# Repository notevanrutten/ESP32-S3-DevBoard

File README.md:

# ESP32-S3-DevBoard

A custom-built development board using the ESP32-S3 chip

## PlatformIO Setup

**NOTE:** This process only needs to be performed once for each development board

1. Download the Zadig driver installation program here: https://zadig.akeo.ie
2. Open Zadig, then click `Options -> List All Devices`
3. Select `USB JTAG/serial debug unit (Interface 0)` and change the driver to **USB Serial (CDC)**
4. Click "Upgrade/Downgrade Driver" (please note, this process may take a few minutes)
5. Select `USB JTAG/serial debug unit (Interface 2)` and change the driver to **libusbK**
6. Click "Upgrade/Downgrade Driver" (please note, this process may take a few minutes)
7. In PlatformIO, configure the platformio.ini file as follows:

   ```ini
    [env:esp32-s3-devboard]

    platform = https://github.com/platformio/platform-espressif32.git
    board = esp32-s3-devkitc-1
    framework = arduino

    upload_speed = 2000000
    monitor_speed = 115200

    debug_tool = esp-builtin
    debug_init_break = break setup
    build_type = debug

    ; enables CDC mode (activates USB-to-Serial)
    build_flags = -DARDUINO_USB_CDC_ON_BOOT=1
   ```

## USB Interface Options

### UART Uploading / Monitoring (Standard)

1. Click the PlatformIO icon on the Activity Bar (left)
2. Navigate to `PROJECT TASKS > esp32-s3-devboard > General > Upload and Monitor` (top left)
3. The firmware will be uploaded automatically and the serial output will be displayed in the terminal

### JTAG Debugging + VCOM Monitoring (Advanced)

1. Click the PlatformIO icon on the Activity Bar (left)
2. Navigate to `QUICK ACCESS > Debug > Start Debugging` (bottom left), or press `F5`
3. The firmware will be uploaded automatically and the debug toolbar will appear (top middle)
4. Use the debug toolbar to Pause/Unpause, Restart, or Stop the program (also has code stepping)
5. To view the serial output while code is unpaused, click `PlatformIO: Serial Monitor` on the Status Bar (bottom)

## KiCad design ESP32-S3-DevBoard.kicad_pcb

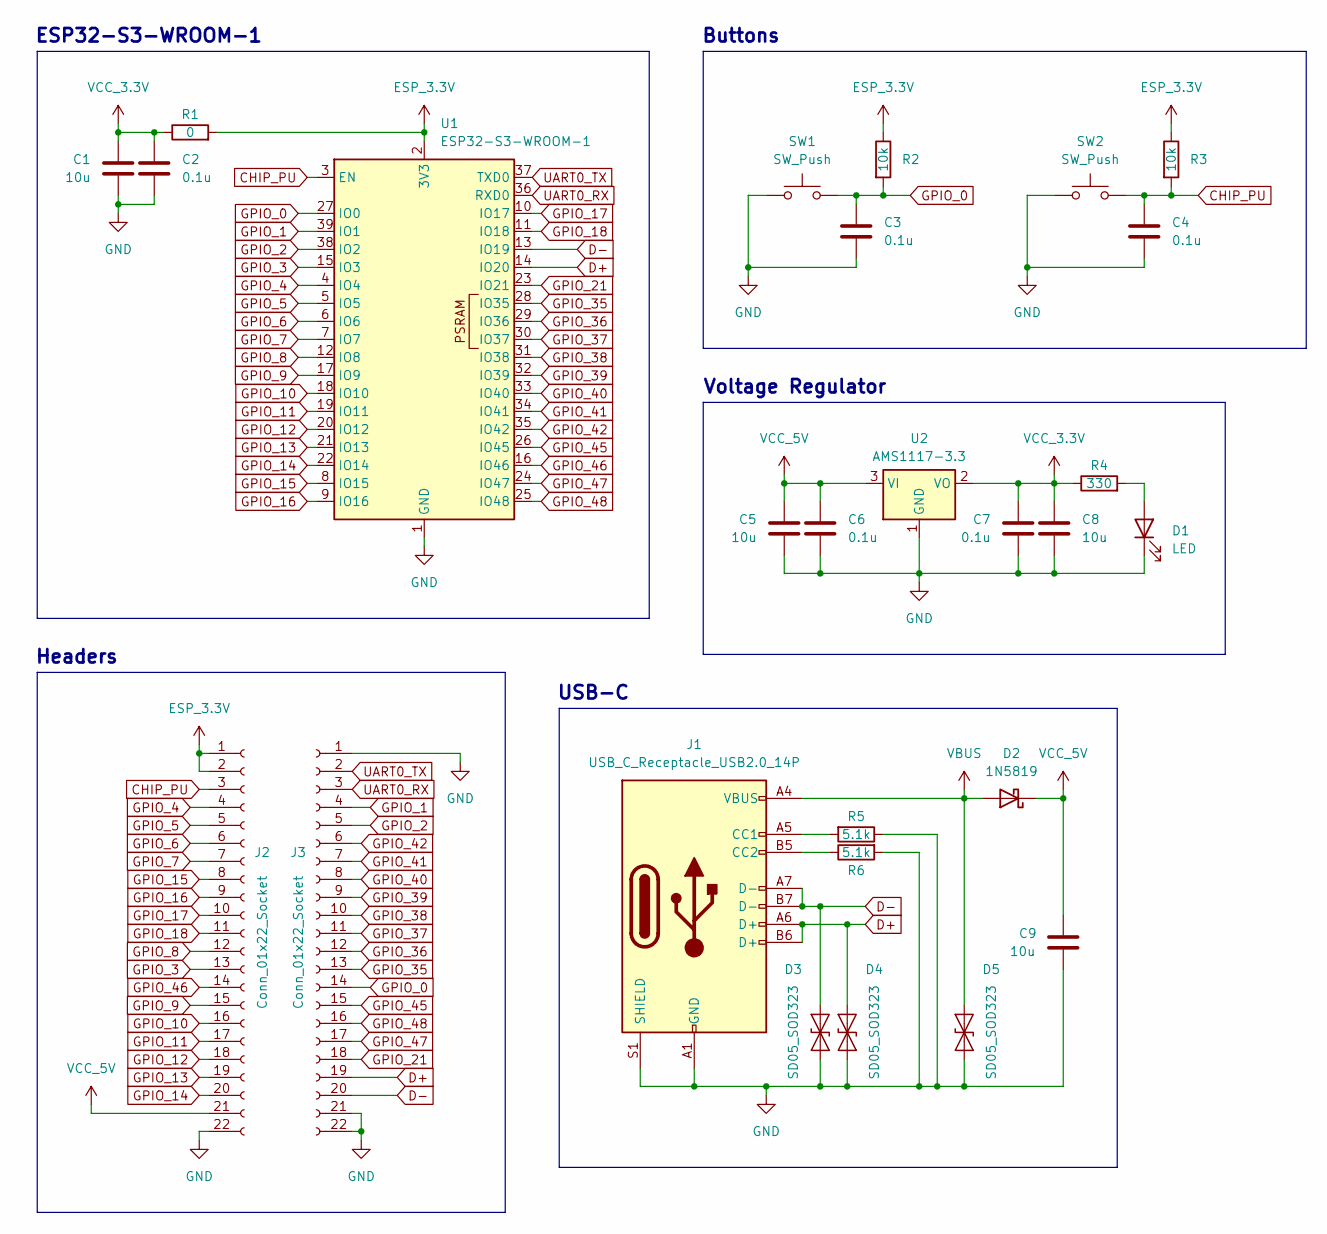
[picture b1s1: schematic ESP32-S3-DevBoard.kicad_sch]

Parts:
C1, C5, C8, C9: 10u; C_0603_1608Metric_Pad1.08x0.95mm_HandSolder
C2, C3, C4, C6, C7: 0.1u; C_0603_1608Metric_Pad1.08x0.95mm_HandSolder
D1: LED; LED_0603_1608Metric_Pad1.05x0.95mm_HandSolder
D2: 1N5819; D_SOD-123
D3, D4, D5: SD05_SOD323; D_SOD-323_HandSoldering
J1: USB_C_Receptacle_USB2.0_14P; USB_C_Receptacle_GCT_USB4105-xx-A_16P_TopMnt_Horizontal
J2, J3: Conn_01x22_Socket; PinSocket_1x22_P2.54mm_Vertical
R1: 0; R_0603_1608Metric_Pad0.98x0.95mm_HandSolder
R2, R3: 10k; R_0603_1608Metric_Pad0.98x0.95mm_HandSolder
R4: 330; R_0603_1608Metric_Pad0.98x0.95mm_HandSolder
R5, R6: 5.1k; R_0603_1608Metric_Pad0.98x0.95mm_HandSolder
SW1, SW2: SW_Push; SW_SPST_PTS810
U1: ESP32-S3-WROOM-1
U2: AMS1117-3.3; SOT-223-3_TabPin2

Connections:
CHIP_PU: C4.1, J2.3, R3.2, SW2.2, U1.3 (EN)
D+: D4.1 (A1), J1.A6 (D+), J1.B6 (D+), J3.19, U1.14 (IO20)
D-: D3.2 (A2), J1.A7 (D-), J1.B7 (D-), J3.20, U1.13 (IO19)
ESP_3.3V: J2.1, J2.2, R1.2, R2.1, R3.1, U1.2 (3V3)
GND: C1.2, C2.2, C3.2, C4.2, C5.2, C6.2, C7.2, C8.2, C9.2, D1.1 (K), D3.1 (A1), D4.2 (A2), D5.1 (A1), J1.A1 (GND), J1.A12 (GND), J1.B1 (GND), J1.B12 (GND), J1.S1 (SHIELD), J2.22, J3.1, J3.21, J3.22, R5.1, R6.2, SW1.1, SW2.1, U1.1 (GND), U1.40 (GND), U1.41 (GND), U2.1 (GND)
GPIO_0: C3.1, J3.14, R2.2, SW1.2, U1.27 (IO0)
GPIO_1: J3.4, U1.39 (IO1)
GPIO_2: J3.5, U1.38 (IO2)
GPIO_3: J2.13, U1.15 (IO3)
GPIO_4: J2.4, U1.4 (IO4)
GPIO_5: J2.5, U1.5 (IO5)
GPIO_6: J2.6, U1.6 (IO6)
GPIO_7: J2.7, U1.7 (IO7)
GPIO_8: J2.12, U1.12 (IO8)
GPIO_9: J2.15, U1.17 (IO9)
GPIO_10: J2.16, U1.18 (IO10)
GPIO_11: J2.17, U1.19 (IO11)
GPIO_12: J2.18, U1.20 (IO12)
GPIO_13: J2.19, U1.21 (IO13)
GPIO_14: J2.20, U1.22 (IO14)
GPIO_15: J2.8, U1.8 (IO15)
GPIO_16: J2.9, U1.9 (IO16)
GPIO_17: J2.10, U1.10 (IO17)
GPIO_18: J2.11, U1.11 (IO18)
GPIO_21: J3.18, U1.23 (IO21)
GPIO_35: J3.13, U1.28 (IO35)
GPIO_36: J3.12, U1.29 (IO36)
GPIO_37: J3.11, U1.30 (IO37)
GPIO_38: J3.10, U1.31 (IO38)
GPIO_39: J3.9, U1.32 (IO39)
GPIO_40: J3.8, U1.33 (IO40)
GPIO_41: J3.7, U1.34 (IO41)
GPIO_42: J3.6, U1.35 (IO42)
GPIO_45: J3.15, U1.26 (IO45)
GPIO_46: J2.14, U1.16 (IO46)
GPIO_47: J3.17, U1.24 (IO47)
GPIO_48: J3.16, U1.25 (IO48)
unnamed: D1.2 (A), R4.2
unnamed: J1.A5 (CC1), R5.2
unnamed: J1.B5 (CC2), R6.1
UART0_RX: J3.3, U1.36 (RXD0)
UART0_TX: J3.2, U1.37 (TXD0)
VBUS: D2.2 (A), D5.2 (A2), J1.A4 (VBUS), J1.A9 (VBUS), J1.B4 (VBUS), J1.B9 (VBUS)
VCC_3.3V: C1.1, C2.1, C7.1, C8.1, R1.1, R4.1, U2.2 (VO)
VCC_5V: C5.1, C6.1, C9.1, D2.1 (K), J2.21, U2.3 (VI)

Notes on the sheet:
USB-C
Buttons
Headers
ESP32-S3-WROOM-1
Voltage Regulator

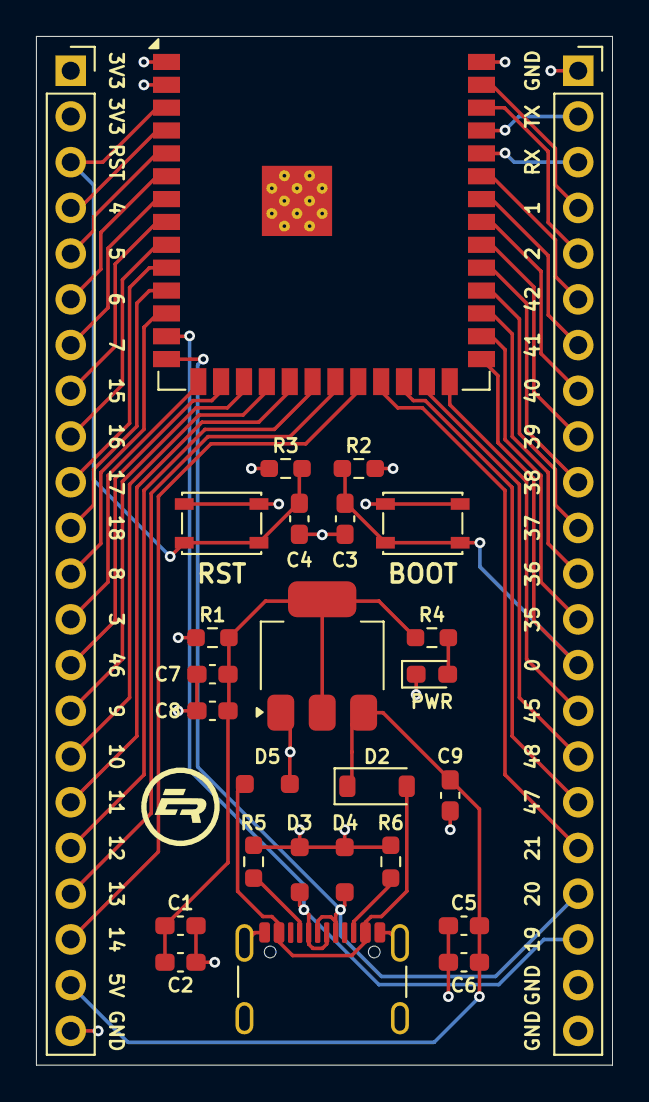
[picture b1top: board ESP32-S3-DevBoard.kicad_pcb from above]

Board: 4 copper layers, 32.0 x 57.1 mm, 27 parts (0 on the bottom side), 45 nets.

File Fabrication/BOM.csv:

Part,Designator,Quantity,LCSC Part #,
10kΩ Resistor,"R2,R3",0,,
PTS810,"SW1,SW2",2,C116501,4
AMS1117-3.3,U2,1,C347222,2
10uF Capacitor,"C1,C5,C8,C9",4,C1691,8
5.1kΩ Resistor,"R5,R6",0,,
0.1uF Capacitor,"C2,C3,C4,C6,C7",5,C1591,10
ESP32-S3-WROOM-1,U1,1,C2913204,2
330Ω Resistor,R4,0,,
1x22 Female Header,"J2,J3",0,,
USB4105,J1,1,C3025063,2
SD05C,"D3,D4,D5",3,C502533,6
LED,D1,0,,
0Ω Resistor,R1,0,,
1N5819,R1,1,C82544,2

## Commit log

2024-06-18 Add USB-C interface
2024-06-18 Remove temp files
2024-06-20 Change to global tags
2024-06-20 Add USB protection
2024-06-20 Add voltage regulator
2024-06-21 Add buttons and decoupled 3.3V
2024-06-21 Decouple remaining power supplies
2024-06-22 Breakout pins to headers
2024-06-23 Add footprints
2024-06-23 Route GPIOs and buttons
2024-06-23 Convert to 4 layer design
2024-06-24 Update USB-C footprint
2024-06-24 Finish layout
2024-06-24 Update PWR/GND planes
2024-06-24 Add space between USB lines
2024-06-24 Add impedance matching for USB lines
2024-06-26 Create gerber files
2024-06-26 Create BOM file
2024-06-26 Show BOM file
2024-06-27 Convert to through-hole vias
2024-06-29 Fix fabrication files
2024-08-15 Add code sample
2024-08-16 Update image size
